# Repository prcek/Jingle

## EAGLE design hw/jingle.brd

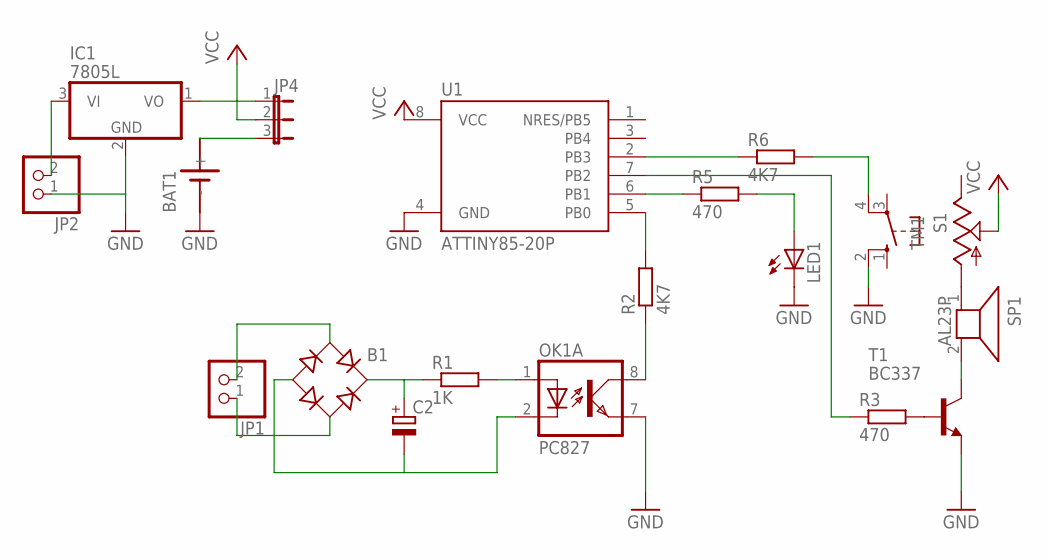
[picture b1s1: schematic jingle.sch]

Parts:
B1: RB1A
BAT1: SN2032
C2: CPOL-EUTT2D5L; TT2D5L
IC1: 7805L; TO92
JP1, JP2: PINHD-1X2; 1X02
JP4: JP2E; JP2
LED1: LED3MM
OK1: PC827; DIL08
R1: 1K; 0207/7
R2, R6: 4K7; 0207/7
R3, R5: 470; 0207/7
S1: 10-XX; B3F-10XX
SP1: AL23P
T1: BC337; TO92
TM1: TRIM; 6MM
U1: ATTINY85-20P; PDIP08_300MIL

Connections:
GND: BAT1.-, IC1.2 (GND), JP2.1, LED1.K (C), OK1.7 (EMIT), S1.2 (S1), T1.1 (E), U1.4 (GND)
unnamed: B1.AC2, JP1.1
unnamed: B1.AC1, JP1.2
unnamed: B1.-, C2.-, OK1.2 (C)
unnamed: B1.+, C2.+, R1.1
unnamed: SP1.2, T1.3 (C)
unnamed: SP1.1, TM1.A
unnamed: OK1.1 (A), R1.2
unnamed: R3.2, T1.2 (B)
unnamed: R5.1, U1.6 (PB1)
unnamed: R2.2, U1.5 (PB0)
unnamed: OK1.8 (COL), R2.1
unnamed: R3.1, U1.7 (PB2)
unnamed: R6.1, U1.2 (PB3)
unnamed: R6.2, S1.4 (P1)
unnamed: LED1.A, R5.2
unnamed: IC1.3 (VI), JP2.2
unnamed: IC1.1 (VO), JP4.1
unnamed: BAT1.+, JP4.3
VCC: JP4.2, TM1.S, U1.8 (VCC)

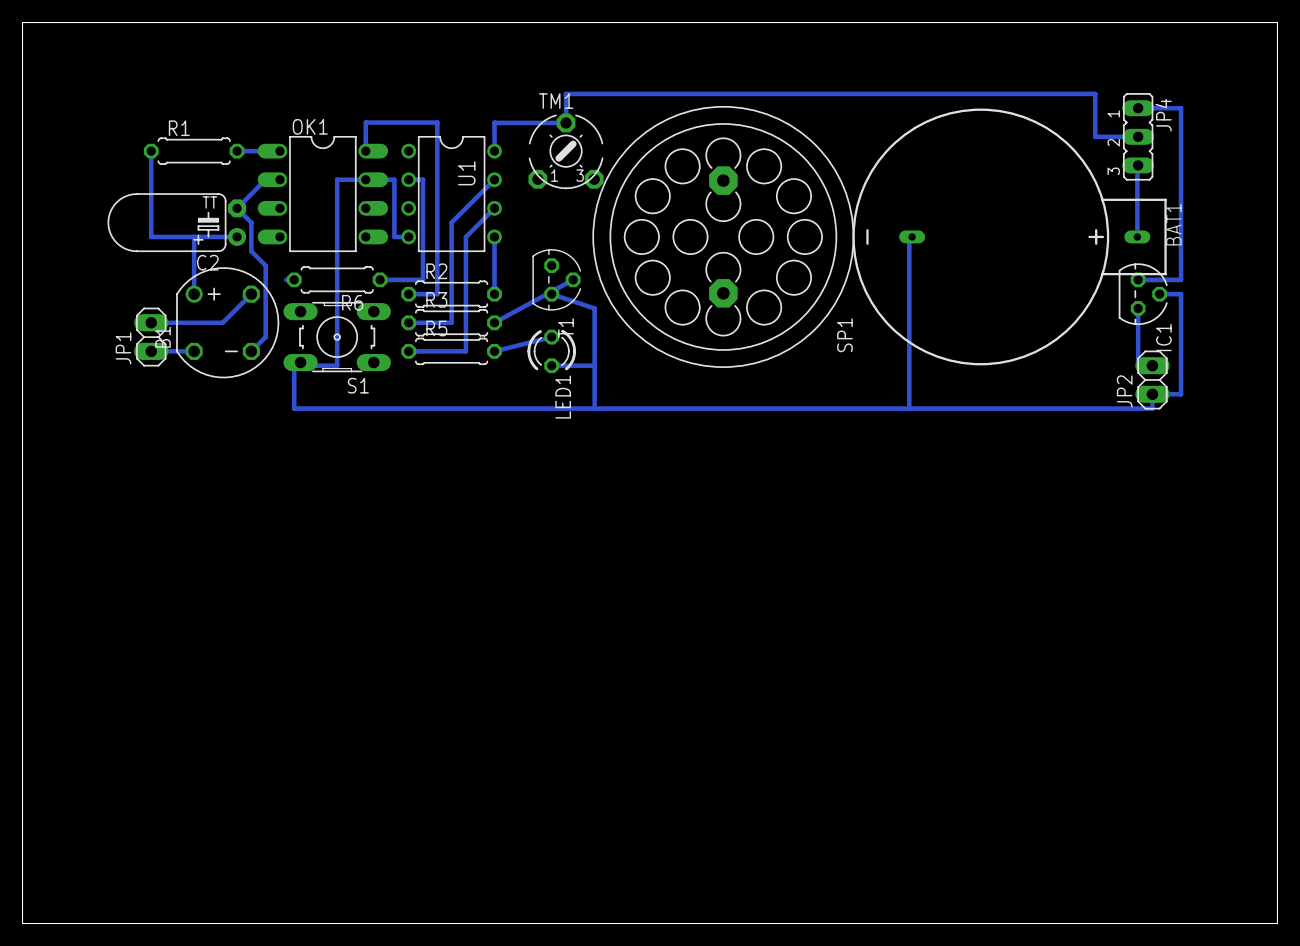
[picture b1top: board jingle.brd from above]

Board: 2 copper layers, 111.4 x 80.0 mm, 19 parts (0 on the bottom side), 20 nets.

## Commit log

2013-09-19 kostra
2013-09-20 Rename test.md to calc.md
2013-09-30 zaklani verze
2013-09-30 hw cast
2013-10-01 deska
2013-10-08 melody test
2013-10-08 cleanup + powermng
2013-10-13 sleep mode
